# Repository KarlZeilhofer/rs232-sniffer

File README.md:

RS232 Sniffer
=============
KiCad Projekt der HTL-Steyr. 

# Features
* MAX3232 für Pegelwandlung von 3.3 V auf RS232 (+-3...15 V)
* UART-Eingänge sind 5V-tolerant
* D-Sub9 Buchse Richtung PC (DTE)
* D-Sub9 Stecker Richtung Gerät (Modem, DCE)
* 2x USB-C Buchse (USB 2.0)
* 2x CH340 USB-UART-Umsetzer
* AM1117-3.3 (Linearregler für 3.3 V aus der 5V USB-Spannung)
* Signal-LEDs (grün = logisch High, rot = logisch Low)
* UART-Stiftleisten für Mikrocontroller
* Programmierbuchse für ESP32/ESP8266

# Anwendungsfälle
## RS232-Sniffer
RS232-Signale werden über D-Sub durchgeleitet. Man sieht dabei die Signal-LEDs entsprechend leuchten/blinken. 
Über die beiden USB-Anschlüsse bzw. die UART-Stiftleisten können die Daten aus beiden Richtungen mitgehorcht werden

## Protokollumsetzer
Die Verbindung der beiden D-Sub Steckverbinder kann aufgetrennt werden, und die Daten können über eine MCU oder einen PC umgeleitet werden. 
Somit können Protokolle angepasst werden bzw. Daten manipuliert werden. 

## USB-UART Adapter
Solche sind zwei Stück verbaut und können auch dirket als solche verwendet werden. 

# Hinweise
## Fertigung
* SMD-Schablone: 120um Dicke, 25mm umlaufender Rand für Pastendrucker
* Leiterplatte: 2 Layer, je 35um Cu, 103x90mm, d=1.6mm, beidseitig Bestückungsdruck
* Lötstopfreistellung: 51um
* min. Lötstopstegbreite: 100um
* Pastenreduktion: umlaufend 40um
* Durchkontaktierungen: blank (nicht mit Lötstopplack bedeckt)

## Besonderes
* Pads der USB-Buchsen wurden minimal verschmälert, um einen Lötstopplack zwischen die Pads zu bekommen.

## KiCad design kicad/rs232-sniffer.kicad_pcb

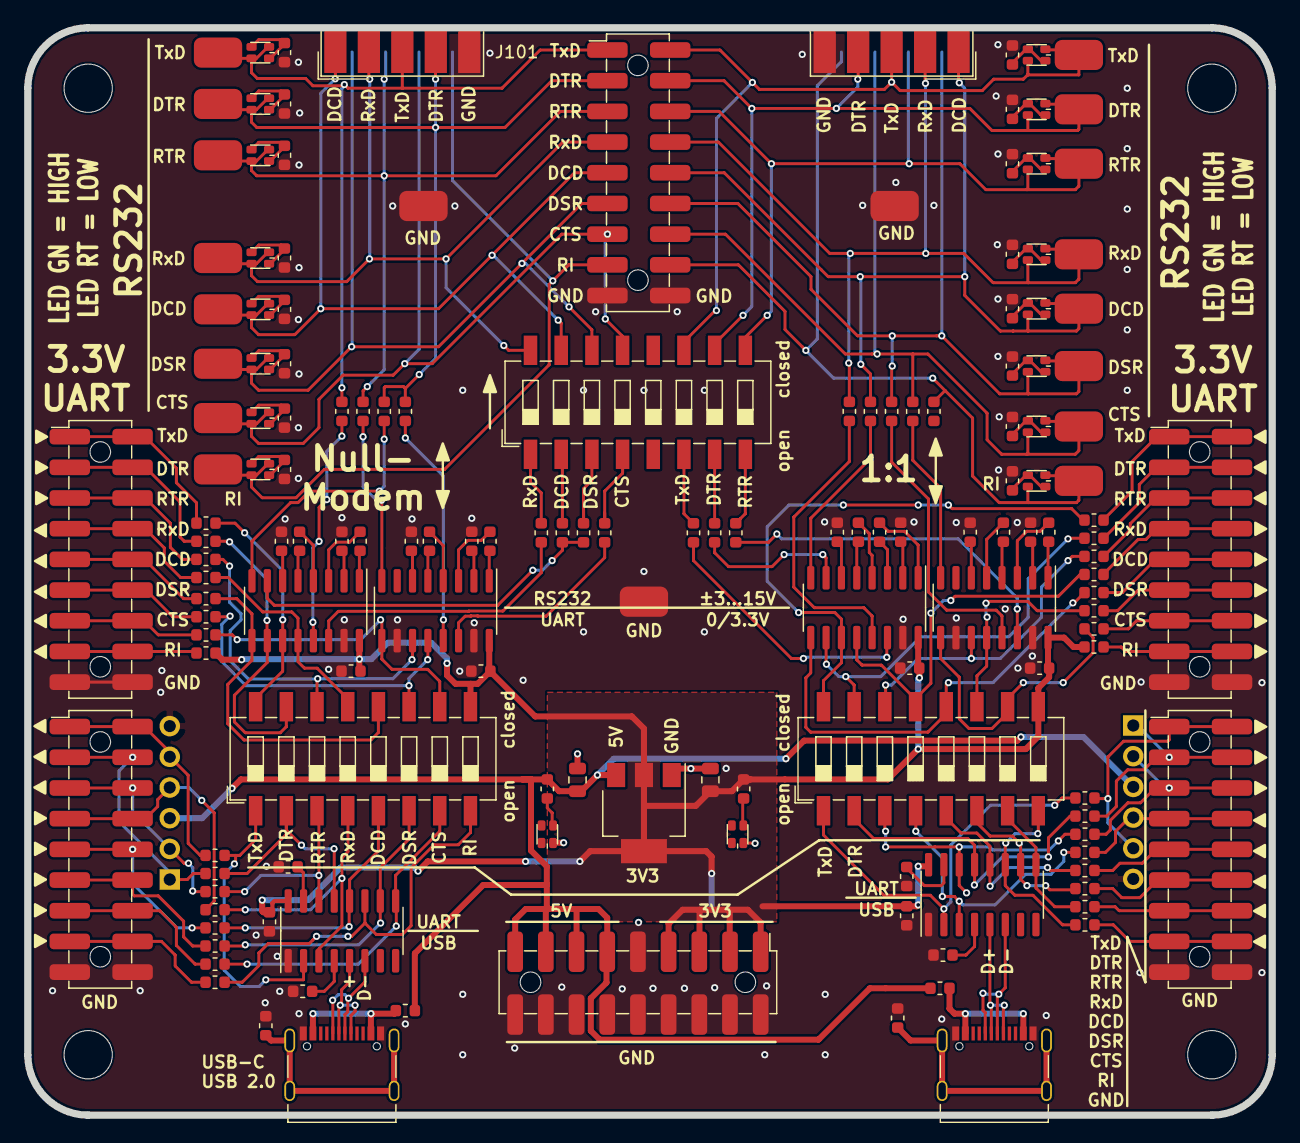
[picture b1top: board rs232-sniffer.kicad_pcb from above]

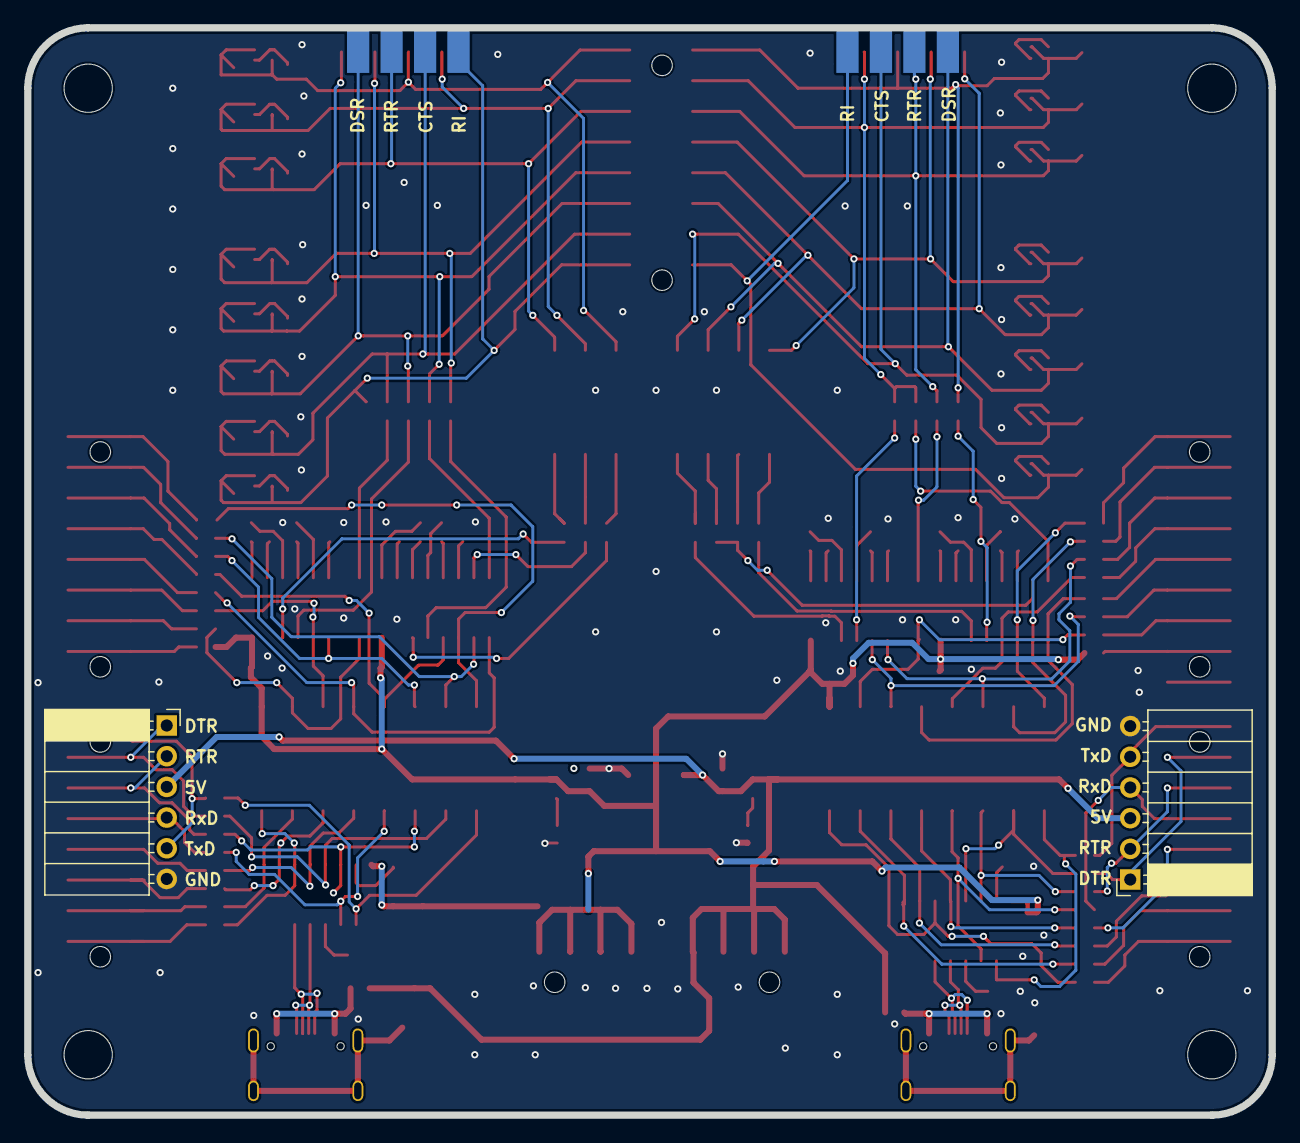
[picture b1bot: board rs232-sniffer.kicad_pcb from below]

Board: 2 copper layers, 103.0 x 90.0 mm, 161 parts (2 on the bottom side), 156 nets.

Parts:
C101, C102: 10u/16V/X5R; C_0805_2012Metric
C2501, C2502, C2503, C2504, C2505, C2506, C2601, C2602, C2603, C2604, C2605, C2606, C2607, C2608, C2609, C2610, C2701, C2702, C2703, C2704, C2705, C2706, C2707, C2708, C2709, C2710: 100n; C_0603_1608Metric
D101, D102, D301, D401, D501, D601, D701, D801, D901, D1001, D1201, D1301, D1401, D1501, D1601, D1701, D1801, D1901: red/green; LED_LiteOn_LTST-C195KGJRKT
H101, H102, H103, H104: MountingHole; MountingHole_4mm
J101: DB9_Female; DSUB-9_Female_EdgeMount_P2.77mm
J102, J104, J2001, J2002, J2401, J2403: Stiftleiste 2x9; PinHeader_2x09_P2.54mm_Vertical_SMD_LCSC_C88175
J103: DB9_Male; DSUB-9_Male_EdgeMount_P2.77mm
J2402, J2405: Buchsenleiste 1x6, horizontal; PinSocket_1x06_P2.54mm_Horizontal
J2501, J2502: USB-C/16p; USB_C_Receptacle_LCSC_C167321
R101, R102, R103, R104, R105, R106, R107, R108, R109, R110, R111, R112, R113, R114, R115, R116, R2004, R2005, R2006, R2007, R2008, R2403, R2404, R2406, R2409, R2410, R2411, R2420, R2421, R2422, R2423, R2424, R2501, R2502: 100R; R_0603_1608Metric
R117, R118: 0R; R_0603_1608Metric
R119, R301, R401, R501, R601, R701, R801, R901, R1001, R1201, R1301, R1401, R1501, R1601, R1701, R1801, R1901: 4k7; R_0603_1608Metric
R120, R2001, R2002, R2003, R2401, R2402, R2405, R2407, R2408, R2412, R2413, R2414, R2415, R2416, R2417, R2418, R2419: 1k; R_0603_1608Metric
SW101, SW2401, SW2402: DIP-Switch 8; SW_DIP_SPSTx08_Slide_6.7x21.88mm_W8.61mm_P2.54mm_LowProfile
TP101, TP102, TP103, TP301, TP401, TP501, TP601, TP701, TP801, TP901, TP1001, TP1201, TP1301, TP1401, TP1501, TP1601, TP1701, TP1801, TP1901: SMD Testpoint; Keystone_5016
U101: AMS1117-3.3; SOT-223-3_TabPin2
U2501, U2502: CH340C; SOIC-16_3.9x9.9mm_P1.27mm
U2601, U2602, U2701, U2702: MAX3232; SOIC-16_3.9x9.9mm_P1.27mm

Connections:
+3V3: C102.1, C2503.2, C2506.2, C2602.2, C2607.2, C2702.2, C2707.2, J104.1, J104.3, J104.5, J104.7, R120.1, R2008.1, R2424.1, SW2401.9, SW2402.9, U101.2, U2501.16, U2502.16, U2601.16, U2602.16, U2701.16, U2702.16
+5V: C101.1, J104.11, J104.13, J104.15, J104.17, J2402.3, J2405.3, R117.2, R118.2, R119.1, U101.3
/LEDs A/Signal1: D301.2, D301.3, J101.1, J102.9, SW101.15, TP301.1
/LEDs A/Signal2: D401.2, D401.3, J101.2, J102.7, SW101.16, TP401.1
/LEDs A/Signal3: D501.2, D501.3, J101.3, J102.1, R101.1, TP501.1
/LEDs A/Signal4: D601.2, D601.3, J101.4, J102.3, R102.1, R103.1, TP601.1
/LEDs A/Signal6: D701.2, D701.3, J101.6, J102.11, SW101.14, TP701.1
/LEDs A/Signal7: D801.2, D801.3, J101.7, J102.5, R104.1, TP801.1
/LEDs A/Signal8: D901.2, D901.3, J101.8, J102.13, SW101.13, TP901.1
/LEDs A/Signal9: D1001.2, D1001.3, J101.9, J102.15, TP1001.1
/LEDs B/Signal1: D1201.2, D1201.3, J102.10, J103.1, R113.1, TP1201.1
/LEDs B/Signal2: D1301.2, D1301.3, J102.8, J103.2, R112.1, TP1301.1
/LEDs B/Signal3: D1401.2, D1401.3, J102.2, J103.3, SW101.11, TP1401.1
/LEDs B/Signal4: D1501.2, D1501.3, J102.4, J103.4, SW101.10, TP1501.1
/LEDs B/Signal6: D1601.2, D1601.3, J102.12, J103.6, R114.1, TP1601.1
/LEDs B/Signal7: D1701.2, D1701.3, J102.6, J103.7, SW101.9, TP1701.1
/LEDs B/Signal8: D1801.2, D1801.3, J102.14, J103.8, R115.1, TP1801.1
/LEDs B/Signal9: D1901.2, D1901.3, J102.16, J103.9, R116.1, TP1901.1
/UART Hub L/RxD: R101.2, U2602.13
/UART Hub L/TxD: R105.1, U2602.14
/UART Hub L/UART - RS232 1/UART_Rx1: R2420.1, SW2402.13, U2602.12
/UART Hub L/UART - RS232 1/UART_Rx2: R2421.1, SW2402.12, U2602.9
/UART Hub L/UART - RS232 1/UART_Tx1: R2417.2, SW2402.16, U2602.11
/UART Hub L/UART - RS232 1/UART_Tx2: R2418.2, SW2402.15, U2602.10
/UART Hub L/UART - RS232 2/UART_Rx1: R2422.1, SW2402.11, U2702.12
/UART Hub L/UART - RS232 2/UART_Rx2: R2423.1, SW2402.10, U2702.9
/UART Hub L/UART - RS232 2/UART_Tx1: R2419.2, SW2402.14, U2702.11
/UART Hub L/USB - UART/D+: J2502.A6, J2502.B6, U2502.5
/UART Hub L/USB - UART/D-: J2502.A7, J2502.B7, U2502.6
/UART Hub L/USB - UART/RxD: R2412.2, SW2402.4, U2502.3
/UART Hub L/USB - UART/TxD: R2409.1, SW2402.1, U2502.2
/UART Hub L/USB - UART/~CTS: R2415.2, SW2402.7, U2502.9
/UART Hub L/USB - UART/~DCD: R2413.2, SW2402.5, U2502.12
/UART Hub L/USB - UART/~DSR: R2414.2, SW2402.6, U2502.10
/UART Hub L/USB - UART/~DTR: R2410.1, SW2402.2, U2502.13
/UART Hub L/USB - UART/~RI: R2416.2, SW2402.8, U2502.11
/UART Hub L/USB - UART/~RTR: R2411.1, SW2402.3, U2502.14
/UART Hub L/USB-Power: J2502.A4, J2502.A9, J2502.B4, J2502.B9, R118.1
/UART Hub L/~CTS: R104.2, U2702.8
/UART Hub L/~DCD: R102.2, U2602.8
/UART Hub L/~DSR: R103.2, U2702.13
/UART Hub L/~DTR: R106.1, R107.1, U2602.7
/UART Hub L/~RTR: R108.1, U2702.14
/UART Hub R/RxD: R112.2, U2601.13
/UART Hub R/TxD: R109.1, U2601.14
/UART Hub R/UART - RS232 1/UART_Rx1: R2004.1, SW2401.13, U2601.12
/UART Hub R/UART - RS232 1/UART_Rx2: R2005.1, SW2401.12, U2601.9
/UART Hub R/UART - RS232 1/UART_Tx1: R2001.2, SW2401.16, U2601.11
/UART Hub R/UART - RS232 1/UART_Tx2: R2002.2, SW2401.15, U2601.10
/UART Hub R/UART - RS232 2/UART_Rx1: R2006.1, SW2401.11, U2701.12
/UART Hub R/UART - RS232 2/UART_Rx2: R2007.1, SW2401.10, U2701.9
/UART Hub R/UART - RS232 2/UART_Tx1: R2003.2, SW2401.14, U2701.11
/UART Hub R/USB - UART/D+: J2501.A6, J2501.B6, U2501.5
/UART Hub R/USB - UART/D-: J2501.A7, J2501.B7, U2501.6
/UART Hub R/USB - UART/RxD: R2401.2, SW2401.4, U2501.3
/UART Hub R/USB - UART/TxD: R2406.1, SW2401.1, U2501.2
/UART Hub R/USB - UART/~CTS: R2407.2, SW2401.7, U2501.9
/UART Hub R/USB - UART/~DCD: R2402.2, SW2401.5, U2501.12
/UART Hub R/USB - UART/~DSR: R2405.2, SW2401.6, U2501.10
/UART Hub R/USB - UART/~DTR: R2403.1, SW2401.2, U2501.13
/UART Hub R/USB - UART/~RI: R2408.2, SW2401.8, U2501.11
/UART Hub R/USB - UART/~RTR: R2404.1, SW2401.3, U2501.14
/UART Hub R/USB-Power: J2501.A4, J2501.A9, J2501.B4, J2501.B9, R117.1
/UART Hub R/~CTS: R115.2, U2701.8
/UART Hub R/~DCD: R113.2, U2601.8
/UART Hub R/~DSR: R114.2, U2701.13
/UART Hub R/~DTR: R110.1, U2601.7
/UART Hub R/~RTR: R111.1, U2701.14
GND: C101.2, C102.2, C2501.1, C2502.2, C2503.1, C2504.1, C2505.2, C2506.1, C2602.1, C2604.1, C2605.1, C2607.1, C2609.1, C2610.1, C2702.1, C2704.1, C2705.1, C2707.1, C2709.1, C2710.1, D101.3, D102.3, J101.5, J102.17, J102.18, J103.5, J104.2, J104.4, J104.6, J104.8, J104.9, J104.10, J104.12, J104.14, J104.16, J104.18, J2001.17, J2001.18, J2002.17, J2002.18, J2401.17, J2401.18, J2402.6, J2403.17, J2403.18, J2405.6, J2501.A1, J2501.A12, J2501.B1, J2501.B12, J2502.A1, J2502.A12, J2502.B1, J2502.B12, R301.2, R401.2, R501.2, R601.2, R701.2, R801.2, R901.2, R1001.2, R1201.2, R1301.2, R1401.2, R1501.2, R1601.2, R1701.2, R1801.2, R1901.2, R2501.2, R2502.2, TP101.1, TP102.1, TP103.1, U101.1, U2501.1, U2502.1, U2601.15, U2602.15, U2701.10, U2701.15, U2702.10, U2702.15
unnamed: C2501.2, J2501.S1
unnamed: C2502.1, U2501.4
unnamed: C2504.2, J2502.S1
unnamed: C2505.1, U2502.4
unnamed: C2601.1, U2601.1
unnamed: C2601.2, U2601.3
unnamed: C2603.1, U2601.4
unnamed: C2603.2, U2601.5
unnamed: C2604.2, U2601.6
unnamed: C2605.2, U2601.2
unnamed: C2606.1, U2602.1
unnamed: C2606.2, U2602.3
unnamed: C2608.1, U2602.4
unnamed: C2608.2, U2602.5
unnamed: C2609.2, U2602.6
unnamed: C2610.2, U2602.2
unnamed: C2701.1, U2701.1
unnamed: C2701.2, U2701.3
unnamed: C2703.1, U2701.4
unnamed: C2703.2, U2701.5
unnamed: C2704.2, U2701.6
unnamed: C2705.2, U2701.2
unnamed: C2706.1, U2702.1
unnamed: C2706.2, U2702.3
unnamed: C2708.1, U2702.4
unnamed: C2708.2, U2702.5
unnamed: C2709.2, U2702.6
unnamed: C2710.2, U2702.2
unnamed: D101.1, R119.2
unnamed: D102.1, R120.2
unnamed: D301.1, D301.4, R301.1
unnamed: D401.1, D401.4, R401.1
unnamed: D501.1, D501.4, R501.1
unnamed: D601.1, D601.4, R601.1
unnamed: D701.1, D701.4, R701.1
unnamed: D801.1, D801.4, R801.1
unnamed: D901.1, D901.4, R901.1
unnamed: D1001.1, D1001.4, R1001.1
unnamed: D1201.1, D1201.4, R1201.1
unnamed: D1301.1, D1301.4, R1301.1
unnamed: D1401.1, D1401.4, R1401.1
unnamed: D1501.1, D1501.4, R1501.1
unnamed: D1601.1, D1601.4, R1601.1
unnamed: D1701.1, D1701.4, R1701.1
unnamed: D1801.1, D1801.4, R1801.1
unnamed: D1901.1, D1901.4, R1901.1
unnamed: J2001.1, J2001.2, J2402.5, R2406.2
unnamed: J2001.3, J2001.4, J2402.1, R2403.2
unnamed: J2001.5, J2001.6, J2402.2, R2404.2
unnamed: J2001.7, J2001.8, J2402.4, R2401.1
unnamed: J2001.9, J2001.10, R2402.1
unnamed: J2001.11, J2001.12, R2405.1
unnamed: J2001.13, J2001.14, R2407.1
unnamed: J2001.15, J2001.16, R2408.1
unnamed: J2002.1, J2002.2, R2001.1
unnamed: J2002.3, J2002.4, R2002.1
unnamed: J2002.5, J2002.6, R2003.1
unnamed: J2002.7, J2002.8, R2004.2
unnamed: J2002.9, J2002.10, R2005.2
unnamed: J2002.11, J2002.12, R2006.2
unnamed: J2002.13, J2002.14, R2007.2
unnamed: J2002.15, J2002.16, R2008.2
unnamed: J2401.1, J2401.2, J2405.5, R2409.2
unnamed: J2401.3, J2401.4, J2405.1, R2410.2
unnamed: J2401.5, J2401.6, J2405.2, R2411.2
unnamed: J2401.7, J2401.8, J2405.4, R2412.1
unnamed: J2401.9, J2401.10, R2413.1
unnamed: J2401.11, J2401.12, R2414.1
unnamed: J2401.13, J2401.14, R2415.1
unnamed: J2401.15, J2401.16, R2416.1
unnamed: J2403.1, J2403.2, R2417.1
unnamed: J2403.3, J2403.4, R2418.1
unnamed: J2403.5, J2403.6, R2419.1
unnamed: J2403.7, J2403.8, R2420.2
unnamed: J2403.9, J2403.10, R2421.2
unnamed: J2403.11, J2403.12, R2422.2
unnamed: J2403.13, J2403.14, R2423.2
unnamed: J2403.15, J2403.16, R2424.2
unnamed: R105.2, SW101.1
unnamed: R106.2, SW101.2
unnamed: R107.2, SW101.3
unnamed: R108.2, SW101.4
unnamed: R109.2, SW101.6
unnamed: R110.2, SW101.7
unnamed: R111.2, SW101.8
unnamed: R2501.1, U2501.15
unnamed: R2502.1, U2502.15

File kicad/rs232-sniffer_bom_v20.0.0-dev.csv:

Component,Description,Part,References,Value,Footprint,Quantity Per PCB,Datasheet,Weblink,DistOrderNr,PriceForQty,PriceEUR,Distributor,ManPartNr,Manufacturer,Notes
1,Unpolarized capacitor,C,C2501 C2502 C2503 C2504 C2505 C2506 C2601 C2602 C2603 C2604 C2605 C2606 C2607 C2608 C2609 C2610 C2701 C2702 C2703 C2704 C2705 C2706 C2707 C2708 C2709 C2710,100n,C_0603_1608Metric,26,https://datasheet.lcsc.com/szlcsc/1811151136_Walsin-Tech-Cor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,https://lcsc.com/product-detail/Multilayer-Ceramic-Capacitor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,C80516,500,0.002141,LCSC,0603B104K160CT,Walsin Tech Corp,100nF ±10% 16V X7R
2,Unpolarized capacitor,C,C101 C102,10u/16V/X5R,C_0805_2012Metric,2,https://datasheet.lcsc.com/szlcsc/1811151151_Samsung-Electro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,https://lcsc.com/product-detail/Multilayer-Ceramic-Capacitor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,C1713,200,0.011386,LCSC,CL21A106KOQNNNE,Samsung,10uF ±10% 16V X5R
3,"Dual LED, cathodes on pins 3 and 4",LED_Dual_AACC,D101 D102 D301 D401 D501 D601 D701 D801 D901 D1001 D1201 D1301 D1401 D1501 D1601 D1701 D1801 D1901,red/green,LED_LiteOn_LTST-C195KGJRKT,18,https://datasheet.lcsc.com/szlcsc/1811100910_Lite-On-LTST-C1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,https://lcsc.com/product-detail/Light-Emitting-Diodes-LED_Li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,C125104,1000,0.023,LCSC,LTST-C195KGJRKT,LiteOn,Dual LED
4,Virtual Item for accessories which should be listed in the BOM,Item,Item1 Item2 Item3 Item4 Item5 Item6 Item7 Item8,Jumper,~,8,https://datasheet.lcsc.com/szlcsc/1811132212_BOOMELE-Boom-Pr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,https://lcsc.com/product-detail/Shunts-Jumpers_BOOMELE-Boom-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,C5305,500,0.00319,LCSC,C5305,BOOMELE(Boom Precision Elec),"Jumper, 2.54mm"
5,"Generic connector, single row, 01x06, script generated (kicad-library-utils/schlib/autogen/connector/)",Conn_01x06,J2402 J2405,"Buchsenleiste 1x6, horizontal",PinSocket_1x06_P2.54mm_Horizontal,2,,,,,,,,,
6,9-pin male D-SUB connector,RS232_DB9_Female,J101,DB9_Female,DSUB-9_Female_EdgeMount_P2.77mm,1,https://datasheet.lcsc.com/szlcsc/1811081030_CONNFLY-Elec-DS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,https://lcsc.com/product-detail/D-Sub-Connectors_D-SUB-9pin-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,C75748,150,0.063911,LCSC,DS1033-09FUNSiSS-CT,CONNFLY Elec,RS232 weiblich
7,9-pin male D-SUB connector,RS232_DB9_Male,J103,DB9_Male,DSUB-9_Male_EdgeMount_P2.77mm,1,,https://lcsc.com/product-detail/D-Sub-Connectors_D-SUB-9pin-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,C75746,150,0.059745,LCSC,DS1033-09MUNSiSS,CONNFLY Elec,RS232 männlich
8,"Generic connector, double row, 02x09, odd/even pin numbering scheme (row 1 odd numbers, row 2 even numbers), script generated (kicad-library-utils/schlib/autogen/connector/)",Conn_02x09_Odd_Even,J102 J104 J2001 J2002 J2401 J2403,Stiftleiste 2x9,PinHeader_2x09_P2.54mm_Vertical_SMD,6,,https://lcsc.com/product-detail/Pin-Header-Female-Header_BOO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,C88175,100,0.036,LCSC,C88175,BOOMELE(Boom Precision Elec),SMD
9,USB 2.0-only Type-C Receptacle connector,USB_C_Receptacle_USB2.0,J2501 J2502,USB-C/16p,USB_C_Receptacle_LCSC_C167321,2,https://www.usb.org/sites/default/files/documents/usb_type-c.zip,https://lcsc.com/product-detail/USB-Connectors_Jing-Extensio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,C167321,100,0.155,LCSC,C167321,Jing Extension,"USB-C, 16-polig, USB 2.0"
10,Resistor,R,R118 R120,0R,R_0603_1608Metric,2,,,,,,LCSC,,,
11,,R_sig,R105 R106 R107 R108 R109 R110 R111 R112 R114 R115 R116 R117 R119 R121 R122 R123 R2004 R2005 R2006 R2007 R2008 R2403 R2404 R2406 R2409 R2410 R2411 R2420 R2421 R2422 R2423 R2424,100R,R_0603_1608Metric,32,https://datasheet.lcsc.com/szlcsc/Uniroyal-Elec-0603WAJ0101T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,https://lcsc.com/product-detail/Chip-Resistor-Surface-Mount_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,C25201,1000,0.000563,LCSC,0603WAJ0101T5E,UNI-ROYAL,"100R, 5%, 100mW"
12,Resistor,R,R2501 R2502,100R,R_0603_1608Metric,2,https://datasheet.lcsc.com/szlcsc/Uniroyal-Elec-0603WAJ0101T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,https://lcsc.com/product-detail/Chip-Resistor-Surface-Mount_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,C25201,1000,0.000563,LCSC,0603WAJ0101T5E,UNI-ROYAL,"100R, 5%, 100mW"
13,,R_sig,R113 R2001 R2002 R2003 R2401 R2402 R2405 R2407 R2408 R2412 R2413 R2414 R2415 R2416 R2417 R2418 R2419,1k,R_0603_1608Metric,17,,https://lcsc.com/product-detail/Chip-Resistor-Surface-Mount_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,C103209,1000,0.000556,LCSC,RTT03102JTP,RALEC,1kΩ ±5% 0.1W ±100ppm/℃
14,Resistor,R,R301 R401 R501 R601 R701 R801 R901 R1001 R1201 R1301 R1401 R1501 R1601 R1701 R1801 R1901,4k7,R_0603_1608Metric,16,https://datasheet.lcsc.com/szlcsc/1809261316_RALEC-RTT03472J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,https://lcsc.com/product-detail/Chip-Resistor-Surface-Mount_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,C103662,1000,0.000527,LCSC,RTT03472JTP,RALEC,4.7kΩ ±5% 0.1W ±100ppm/℃
15,,R_sig,R104,4k7,R_0603_1608Metric,1,https://datasheet.lcsc.com/szlcsc/1809261316_RALEC-RTT03472J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,https://lcsc.com/product-detail/Chip-Resistor-Surface-Mount_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,C103662,1000,0.000527,LCSC,RTT03472JTP,RALEC,4.7kΩ ±5% 0.1W ±100ppm/℃
16,"8x DIP Switch, Single Pole Single Throw (SPST) switch, small symbol",SW_DIP_x08,SW101 SW2401 SW2402,DIP-Switch 8,SW_DIP_SPSTx08_Slide_6.7x21.88mm_W8.61mm_P2.54mm_LowProfile,3,https://datasheet.lcsc.com/szlcsc/Made-in-China-HAD-08HWA-R_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,https://lcsc.com/product-detail/DIP-Switches_Cixi-Tonver-Ele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,C4682,100,0.262623,LCSC,HAD-08HWA-R,Cixi Tonver Elec,SMD DIP-Switch
17,"1A Low Dropout regulator, positive, 3.3V fixed output, SOT-223",AMS1117-3.3,U101,AMS1117-3.3,SOT-223-3_TabPin2,1,http://www.advanced-monolithic.com/pdf/ds1117.pdf,https://lcsc.com/products/Dropout-Regulators-LDO_387.html?q=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,C347222,100,0.023029,LCSC,AMS1117-3.3,UMW Youtai Semiconductor,"LDO, 3.3V"
18,"USB serial converter, UART, SOIC-16",CH340C,U2501 U2502,CH340C,SOIC-16_3.9x9.9mm_P1.27mm,2,http://www.datasheet5.com/pdf-local-2195953,https://lcsc.com/product-detail/USB-ICs_WCH-Jiangsu-Qin-Heng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,C84681,100,0.239,LCSC,CH340C,WCH(Jiangsu Qin Heng),USB-UART with internal clock
19,"3.0V to 5.5V, Low-Power, up to 1Mbps, True RS-232 Transceivers Using Four 0.1μF External Capacitors",MAX3232,U2601 U2602 U2701 U2702,MAX3232,SOIC-16_3.9x9.9mm_P1.27mm,4,https://datasheets.maximintegrated.com/en/ds/MAX3222-MAX3241.pdf,https://lcsc.com/product-detail/Uncategorized_HGSEMI-MAX3232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,C434486,100,0.188404,LCSC,MAX3232EIM/TR,HGSEMI,"RS232 - UART Umsetzer, 3V3 oder 5V"





Component Groups:,19
Component Count:,146
Fitted Components:,146
Number of PCBs:,1
Total components:,146
Schematic Version:,v20.0.0-dev
Schematic Date:,2020-10-09
PCB Variant:,[u'default']
BoM Date:,2020-10-13T15:02:37 CEST
Schematic Source:,rs232-sniffer.sch
KiCad Version:,Eeschema 5.1.6-c6e7f7d~87~ubuntu18.04.1

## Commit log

2019-12-16 erste version zeilhofer
2019-12-16 version marius wasinger
2019-12-16 3D files Testpunkt
2020-11-11 übergabe an 3ahel
2020-11-11 Layout fast fertig Footprint für 2x9-polig wurde aktualisiert
2020-11-12 manual merge with master
2020-11-13 fertig geroutet
2020-11-13 V20.0.0 fertig zur Leiterplattenbestellung, BOM export, PDF, Gerber
2020-11-13 readme update
2020-11-13 Korrekturen bez. SMD-Schablone, angepasst an Mulit-CB
2020-11-13 Bild in Readme
2021-03-15 Schaltplan Kompakt exportiert
2021-03-15 rework gestartet
2021-03-17 Keine SMD-Paste bei den Steckverbindern
2021-03-17 v20.0.1 fertig, 30 Stk bestellt
2021-03-26 HTML BOM V20.0.1
2021-06-09 added PDF and SVG files
2021-09-29 BOM vervollständigt
2021-09-29 postcommit
